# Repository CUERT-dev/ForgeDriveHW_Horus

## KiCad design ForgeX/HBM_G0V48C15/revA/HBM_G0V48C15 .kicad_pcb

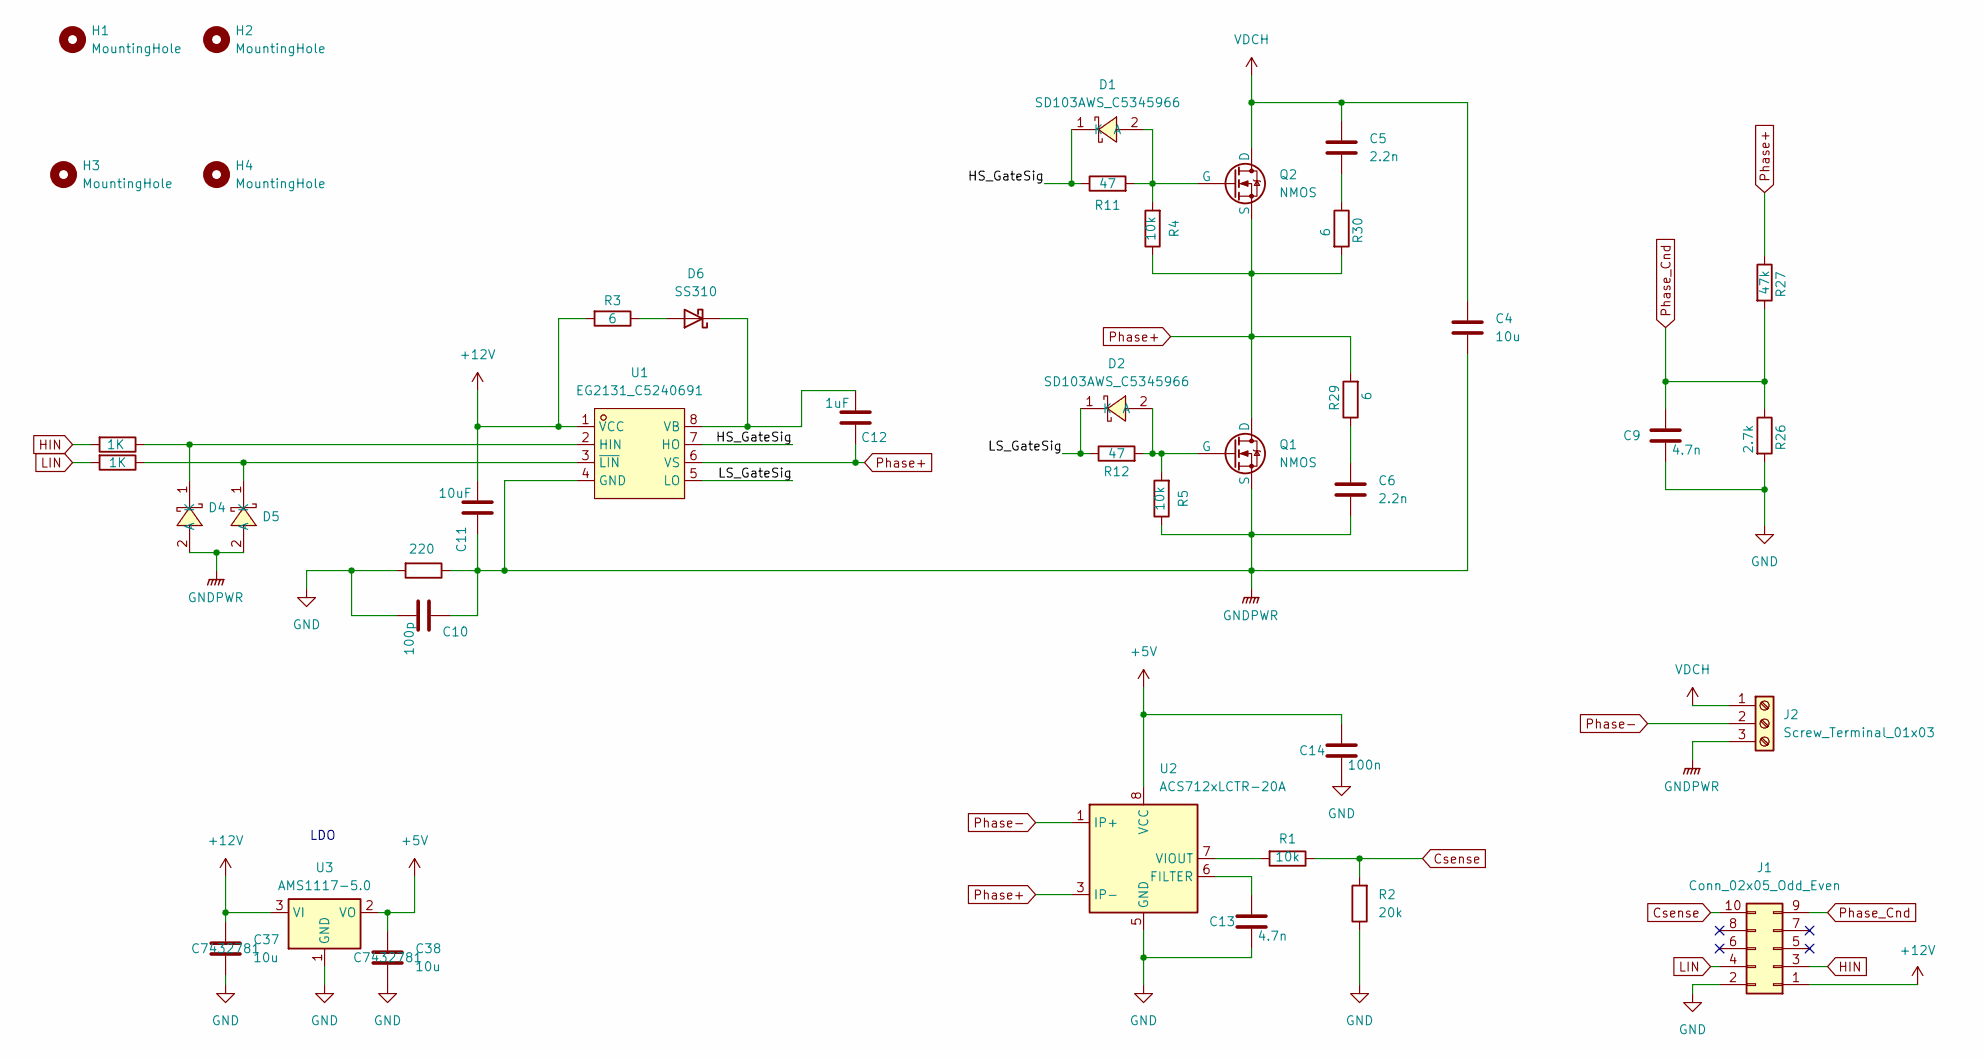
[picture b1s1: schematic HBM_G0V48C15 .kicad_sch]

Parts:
C4: 10u; C_1210_3225Metric_Pad1.33x2.70mm_HandSolder
C5, C6: 2.2n; C_1206_3216Metric_Pad1.33x1.80mm_HandSolder
C9, C13: 4.7n; C_0603_1608Metric_Pad1.08x0.95mm_HandSolder
C10: 100p; C_1206_3216Metric_Pad1.33x1.80mm_HandSolder
C11: 10uF; C_1206_3216Metric_Pad1.33x1.80mm_HandSolder
C12: 1uF; C_1206_3216Metric_Pad1.33x1.80mm_HandSolder
C14: 100n; C_0603_1608Metric_Pad1.08x0.95mm_HandSolder
C37, C38: 10u; C_1206_3216Metric_Pad1.33x1.80mm_HandSolder; LCSC Part C7432781
D1, D2, D4, D5: SD103AWS_C5345966; SOD-323_L1.7-W1.3-LS2.5-RD; MPN SD103AWS; LCSC Part C5345966
D6: SS310; D_SMA
H1, H2: MountingHole; MountingHole_3.2mm_M3_DIN965
H3, H4: MountingHole; MountingHole_2.2mm_M2_DIN965
J1: Conn_02x05_Odd_Even; PinHeader_2x05_P2.54mm_Vertical
J2: Screw_Terminal_01x03; SPACER_M3_PCONN_2x03
Q1, Q2: NMOS; DFN5x6
R1, R4, R5: 10k; R_0603_1608Metric_Pad0.98x0.95mm_HandSolder
R2: 20k; R_0603_1608Metric_Pad0.98x0.95mm_HandSolder
R3: 6; R_0603_1608Metric_Pad0.98x0.95mm_HandSolder
R8: 220; R_1206_3216Metric_Pad1.30x1.75mm_HandSolder
R9, R10: 1K; R_0603_1608Metric_Pad0.98x0.95mm_HandSolder
R11, R12: 47; R_0603_1608Metric_Pad0.98x0.95mm_HandSolder
R26: 2.7k; R_0603_1608Metric_Pad0.98x0.95mm_HandSolder
R27: 47k; R_1206_3216Metric_Pad1.30x1.75mm_HandSolder
R29, R30: 6; R_1206_3216Metric_Pad1.30x1.75mm_HandSolder
U1: EG2131_C5240691; SOP-8_L4.9-W3.9-P1.27-LS6.0-BL; MPN EG2131; LCSC Part C5240691
U2: ACS712xLCTR-20A; SOIC-8_3.9x4.9mm_P1.27mm
U3: AMS1117-5.0; SOT-89-3

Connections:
+5V: C14.1, C38.1, U2.8 (VCC), U3.2 (VO)
+12V: C11.2, C37.1, J1.1, R3.2, U1.1 (VCC), U3.3 (VI)
/HS_GateSig: D1.1 (K), R11.1, U1.7 (HO)
/LS_GateSig: D2.1 (K), R12.1, U1.5 (LO)
Csense: J1.10, R1.1, R2.2
GND: C9.2, C10.2, C13.2, C14.2, C37.2, C38.2, J1.2, R2.1, R8.2, R26.2, U2.5 (GND), U3.1 (GND)
GNDPWR: C4.2, C6.1, C10.1, C11.1, D4.2 (A), D5.2 (A), J2.3, Q1.3 (S), R5.1, R8.1, U1.4 (GND)
HIN: J1.3, R9.2
LIN: J1.4, R10.2
unnamed: C5.2, R30.1
unnamed: C6.2, R29.1
unnamed: D1.2 (A), Q2.2 (G), R4.2, R11.2
unnamed: D2.2 (A), Q1.2 (G), R5.2, R12.2
unnamed: D4.1 (K), R9.1, U1.2 (HIN)
unnamed: D5.1 (K), R10.1, U1.3 (~LIN)
unnamed: D6.2 (A), R3.1
unnamed: C12.2, D6.1 (K), U1.8 (VB)
unnamed: C13.1, U2.6 (FILTER)
unnamed: R1.2, U2.7 (VIOUT)
Phase+: C12.1, Q1.1 (D), Q2.3 (S), R4.1, R27.1, R29.2, R30.2, U1.6 (VS), U2.3 (IP-), U2.4 (IP-)
Phase-: J2.2, U2.1 (IP+), U2.2 (IP+)
Phase_Cnd: C9.1, J1.9, R26.1, R27.2
VDCH: C4.1, C5.1, J2.1, Q2.1 (D)

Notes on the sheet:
LDO

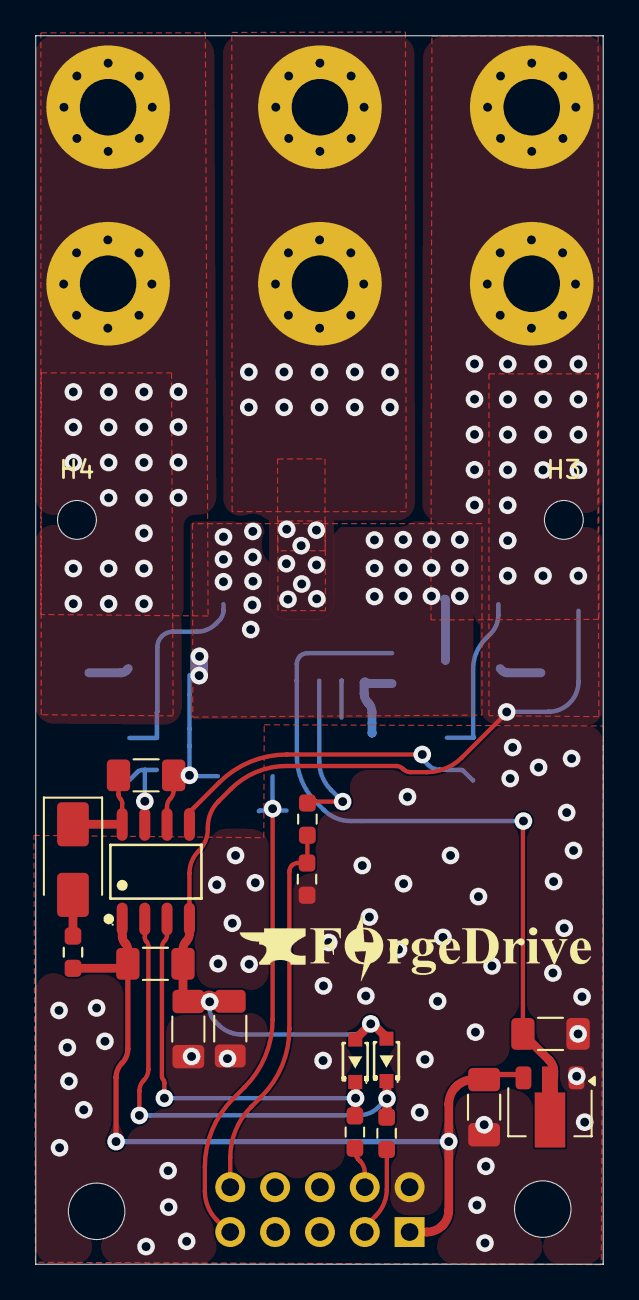
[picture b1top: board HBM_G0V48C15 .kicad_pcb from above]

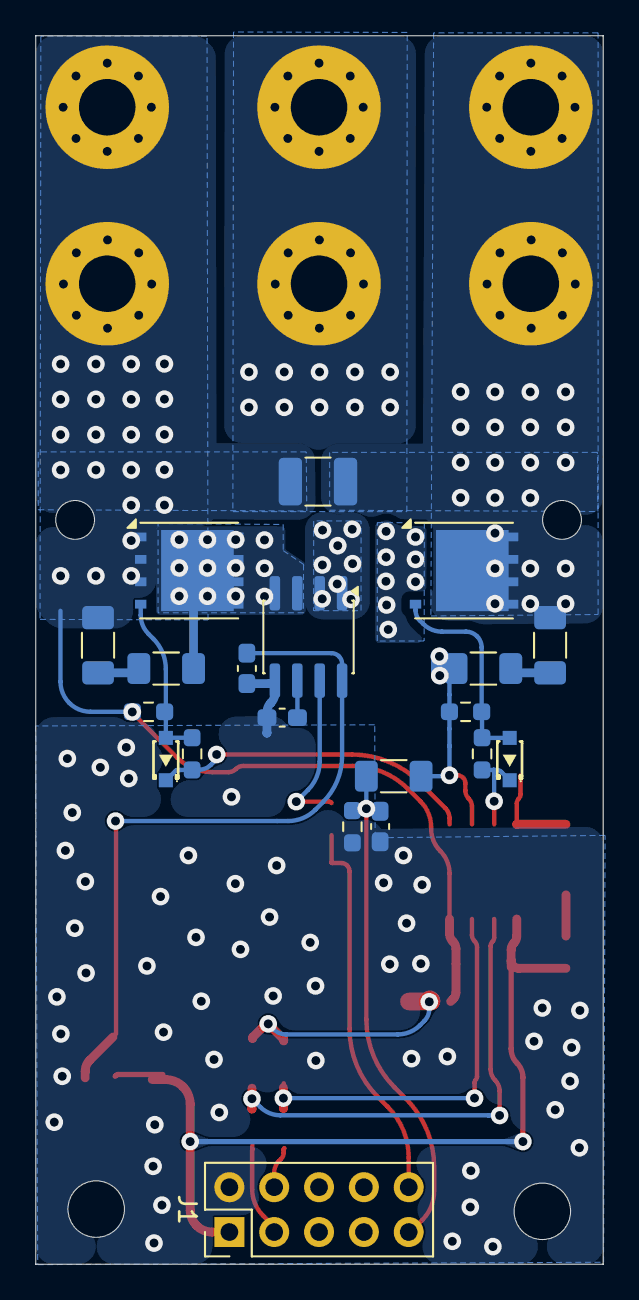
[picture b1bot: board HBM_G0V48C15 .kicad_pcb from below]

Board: 2 copper layers, 32.2 x 69.6 mm, 41 parts (20 on the bottom side), 23 nets.

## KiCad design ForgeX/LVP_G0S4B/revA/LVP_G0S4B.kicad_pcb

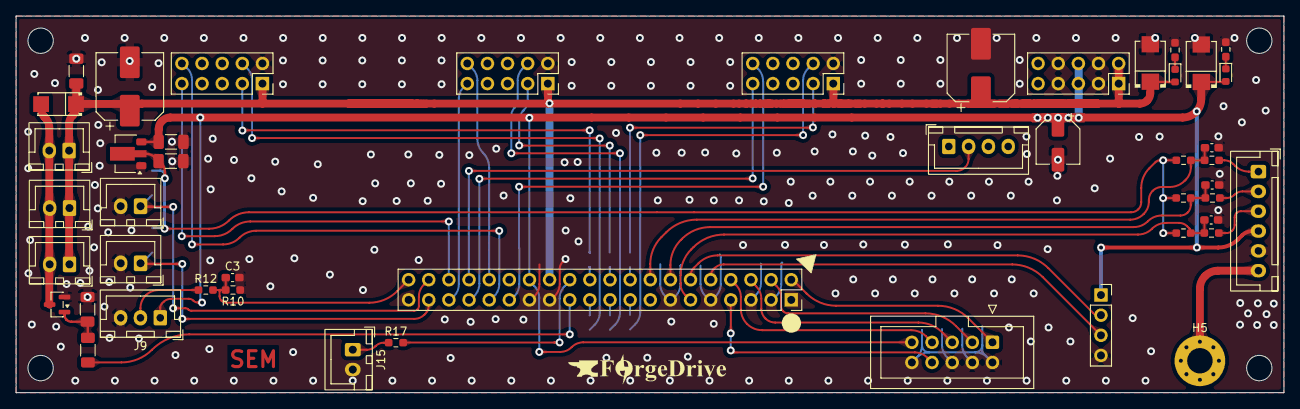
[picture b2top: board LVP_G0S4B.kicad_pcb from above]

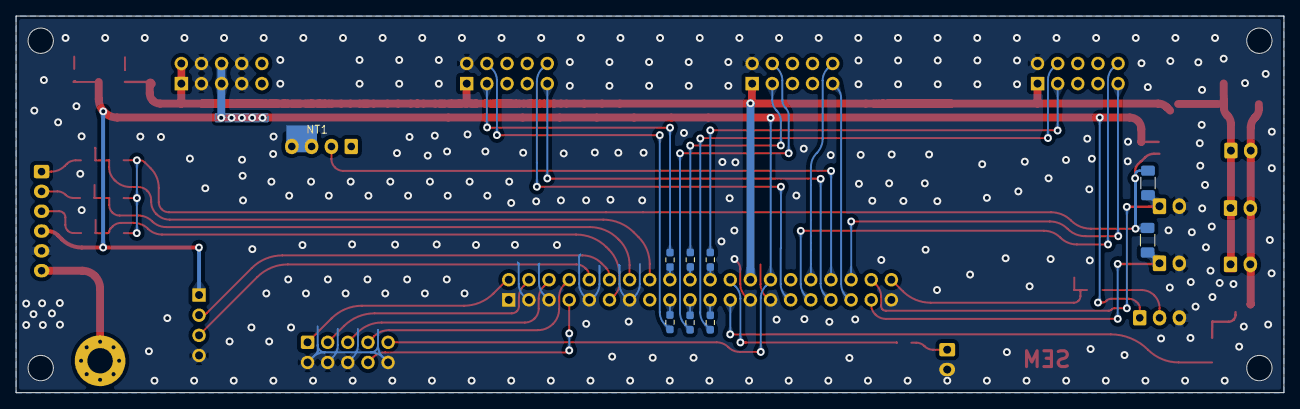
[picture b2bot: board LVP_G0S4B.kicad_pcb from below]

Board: 2 copper layers, 159.9 x 47.5 mm, 60 parts (9 on the bottom side), 49 nets.

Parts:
C1, C2, C6: 10u; C_1206_3216Metric_Pad1.33x1.80mm_HandSolder
C3: 100n; C_0603_1608Metric_Pad1.08x0.95mm_HandSolder
C8: 47uF; CP_Elec_5x5.4
C9, C10: 100uF; CP_Elec_8x6.5
C11, C12, C13: 100p; C_0603_1608Metric_Pad1.08x0.95mm_HandSolder
D1, D3: LED; LED_0603_1608Metric
D2: SS34_C8678; SMA_L4.3-W2.6-LS5.2-RD
D4: SMBJ5.0A_C83333; SMB_L4.6-W3.6-LS5.3-RD
D5: SMBJ12A_C151251; SMB_L4.6-W3.6-LS5.3-RD
H1, H2, H3, H4: MountingHole; MountingHole_3.2mm_M3_DIN965
H5: MountingHole_Pad; MountingHole_3.2mm_M3_Pad_Via
J1, J2, J3, J4: Conn_02x05_Odd_Even; PinSocket_2x05_P2.54mm_Vertical
J5: Conn_01x06_Pin; JST_XH_B6B-XH-A_1x06_P2.50mm_Vertical
J6: Conn_02x20_Odd_Even; PinSocket_2x20_P2.54mm_Vertical
J7, J8, J11, J12, J13, J15: Conn_01x02_Pin; JST_XH_B2B-XH-A_1x02_P2.50mm_Vertical
J9: Conn_01x03_Pin; JST_XH_B3B-XH-A_1x03_P2.50mm_Vertical
J14: Conn_02x05_Odd_Even; IDC-Header_2x05_P2.54mm_Vertical
J16: Conn_01x04; PinSocket_1x04_P2.54mm_Vertical
J17: Conn_01x04; JST_XH_B4B-XH-A_1x04_P2.50mm_Vertical
NT1: NetTie_2; ground_tie
Q2: AO3400A; SOT-23
R1, R2, R3, R4, R5, R6, R14, R15, R18: 220; R_0603_1608Metric_Pad0.98x0.95mm_HandSolder
R7, R16, R17: 1k; R_0603_1608Metric_Pad0.98x0.95mm_HandSolder
R8, R9, R11: 20k; R_1206_3216Metric_Pad1.30x1.75mm_HandSolder
R10: 20k; R_0603_1608Metric_Pad0.98x0.95mm_HandSolder
R12: 10k; R_0603_1608Metric_Pad0.98x0.95mm_HandSolder
R13: 2k; R_1206_3216Metric_Pad1.30x1.75mm_HandSolder
R19, R20, R21: 2.2k; R_0603_1608Metric_Pad0.98x0.95mm_HandSolder
U4: AMS1117-3.3; SOT-89-3

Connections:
+3.3V: C2.1, R8.2, R9.2, R19.2, R20.2, R21.2, U4.2 (VO)
+5V: C1.1, C8.1, D3.2 (A), D4.1, J4.5, J4.6, J5.4, J6.28, J9.1, J14.9, J16.1, U4.3 (VI)
+12V: C6.1, C9.1, C10.1, D1.2 (A), D2.1 (K), D5.1 (K), J1.1, J2.1, J3.1, J4.1, J4.2, J6.26, J11.1, J12.1, J13.1
/Csense_{A}: J3.10, J6.29
/Csense_{B}: J2.10, J6.32
/Csense_{C}: J1.10, J6.31
/ENC_R1: C11.1, J6.16, R14.1, R19.1
/ENC_R1_IN: J5.1, R14.2
/ENC_R2: C12.1, J6.14, R15.1, R20.1
/ENC_R2_IN: J5.2, R15.2
/ENC_R3: C13.1, J6.11, R18.1, R21.1
/ENC_R3_IN: J5.3, R18.2
/EXP_CS0: J6.8, J14.7
/EXP_CS1: J6.7, J14.8
/EXP_MISO: J6.6, J14.5
/EXP_MOSI: J6.4, J14.3
/EXP_RX: J6.12, J16.2
/EXP_SCLK: J6.2, J14.1
/EXP_TX: J6.10, J16.3
/FAN0: J6.23, R13.2
/HIN_{A}: J3.3, R1.2
/HIN_{B}: J2.3, R3.2
/HIN_{C}: J1.3, R4.2
/HVDC_Cnd: J6.34, J17.2
/LIN_{A}: J3.4, R2.1
/LIN_{B}: J2.4, R5.1
/LIN_{C}: J1.4, R6.1
/Phase_Cnd_{A}: J3.9, J6.33
/Phase_Cnd_{B}: J2.9, J6.35
/Phase_Cnd_{C}: J1.9, J6.36
/TEMP1: J6.38, J7.1, R8.1
/TEMP2: J6.37, J8.1, R9.1
/THROTTLE: C3.1, J6.40, R10.2, R12.2
/~BKIN: J6.24, R17.2
Earth: H5.1 (1_1), J5.6
GND: C1.2, C2.2, C3.2, C6.2, C8.2, C9.2, C10.2, C11.2, C12.2, C13.2, D4.2, D5.2 (A), J1.2, J2.2, J3.2, J4.3, J4.4, J4.7, J4.8, J5.5, J6.1, J6.3, J6.5, J6.9, J6.13, J6.25, J6.27, J6.39, J7.2, J8.2, J9.3, J14.2, J14.4, J14.6, J14.10, J15.2, J16.4, NT1.2, Q2.2 (S), R7.2, R10.1, R11.1, R16.2, U4.1 (GND)
GNDPWR: J17.3, J17.4, NT1.1
unnamed: D1.1 (K), R7.1
unnamed: D2.2 (A), J11.2, J12.2, J13.2, Q2.3 (D)
unnamed: D3.1 (K), R16.1
unnamed: J6.17, R2.2
unnamed: J6.18, R1.1
unnamed: J6.19, R5.2
unnamed: J6.20, R3.1
unnamed: J6.21, R6.2
unnamed: J6.22, R4.1
unnamed: J9.2, R12.1
unnamed: J15.1, R17.1
unnamed: Q2.1 (G), R11.2, R13.1

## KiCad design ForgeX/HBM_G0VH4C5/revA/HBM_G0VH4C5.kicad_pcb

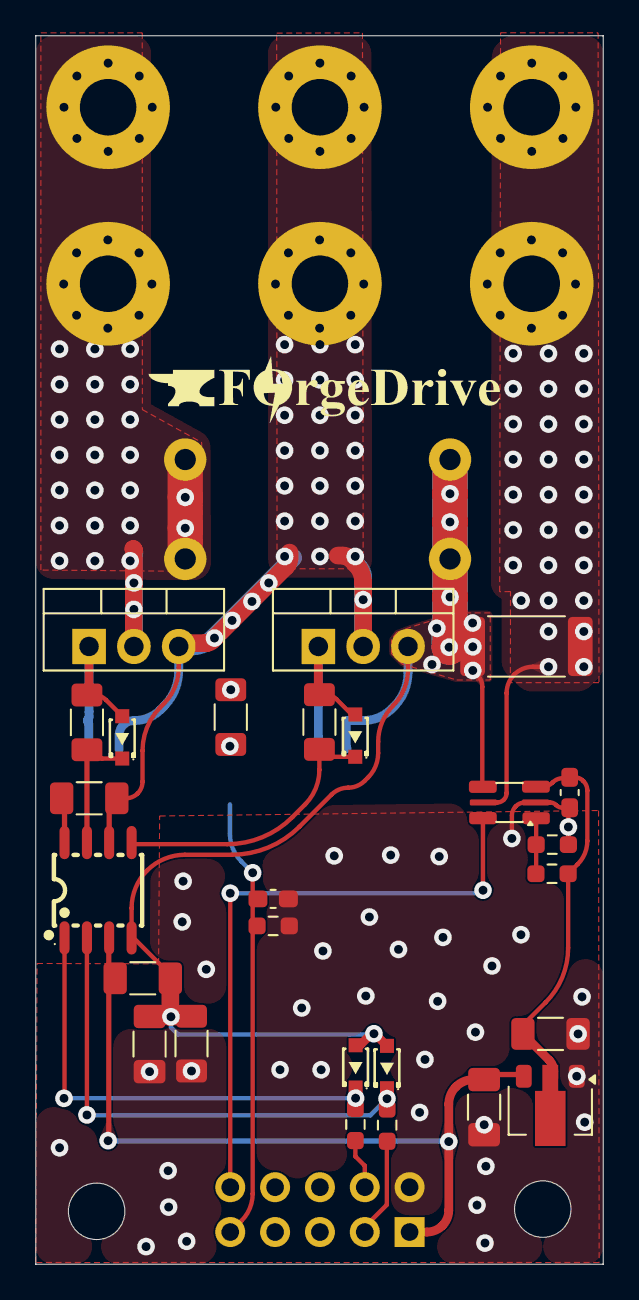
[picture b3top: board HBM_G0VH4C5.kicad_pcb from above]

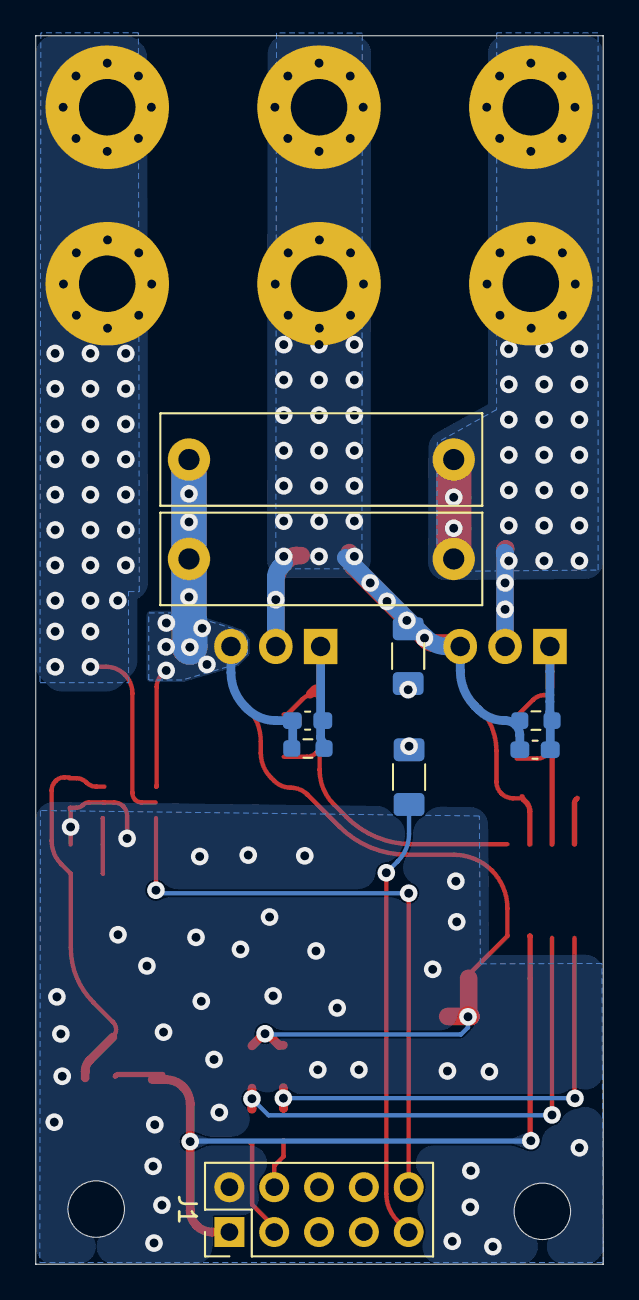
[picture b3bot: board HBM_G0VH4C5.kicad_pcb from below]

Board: 2 copper layers, 32.2 x 69.6 mm, 38 parts (9 on the bottom side), 21 nets.

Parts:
C2, C3: 1n; C_0603_1608Metric_Pad1.08x0.95mm_HandSolder
C4: 0.1u; C_0603_1608Metric_Pad1.08x0.95mm_HandSolder
C7: 10uF; C_1206_3216Metric_Pad1.33x1.80mm_HandSolder
C8: 1u; C_1206_3216Metric_Pad1.33x1.80mm_HandSolder
C9: 47n; C_0603_1608Metric_Pad1.08x0.95mm_HandSolder
C10: 100p; C_1206_3216Metric_Pad1.33x1.80mm_HandSolder
C20, C21: 1u; C_Rect_L18.0mm_W5.0mm_P15.00mm_FKS3_FKP3
C37, C38: 10u; C_1206_3216Metric_Pad1.33x1.80mm_HandSolder
D1, D2, D3, D4: SD103AWS_C5345966; SOD-323_L1.7-W1.3-LS2.5-RD
H1, H2: MountingHole; MountingHole_3.2mm_M3_DIN965
J1: Conn_02x05_Odd_Even; PinHeader_2x05_P2.54mm_Vertical
J2: Screw_Terminal_01x03; SPACER_M3_PCONN_2x03
Q1, Q2: STF24N60M2; TO-220-3_Vertical
R1: 5m; R_2512_6332Metric_Pad1.40x3.35mm_HandSolder
R2, R3, R4, R5: 10k; R_0603_1608Metric_Pad0.98x0.95mm_HandSolder
R6, R7: 1k; R_0603_1608Metric_Pad0.98x0.95mm_HandSolder
R8: 220; R_1206_3216Metric_Pad1.30x1.75mm_HandSolder
R11, R12: 10; R_1206_3216Metric_Pad1.30x1.75mm_HandSolder
R26: 3.3k; R_0603_1608Metric_Pad0.98x0.95mm_HandSolder
R27, R28, R29: 150k; R_1206_3216Metric_Pad1.30x1.75mm_HandSolder
U1: INA199xxDCK; SOT-363_SC-70-6
U3: L6388ED; SO-8_L4.9-W3.9-P1.27-LS5.9-BL
U7: AMS1117-3.3; SOT-89-3

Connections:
+3.3V: C4.1, C38.1, R2.2, U1.3 (V+), U7.2 (VO)
+12V: C7.1, C37.1, J1.1, U3.3 (VCC), U7.3 (VI)
/HS_GateSig: D1.1 (K), R11.1, U3.7 (HVG)
/LS_GateSig: D2.1 (K), R12.1, U3.5 (LVG)
/Shunt+: C2.2, C7.2, C10.1, C20.2, C21.2, D3.2 (A), D4.2 (A), Q1.3 (S), R1.1, R5.1, R8.1, U1.4 (+), U3.4 (GND)
Csense: J1.10, U1.6
GND: C4.2, C9.2, C10.2, C37.2, C38.2, J1.2, R3.1, R8.2, R26.2, U1.2 (GND), U7.1 (GND)
GNDPWR: J2.3, R1.2, U1.5 (-)
HIN: J1.3, R7.1
LIN: J1.4, R6.1
unnamed: C3.1, D1.2 (A), Q2.1 (G), R4.2, R11.2
unnamed: C2.1, D2.2 (A), Q1.1 (G), R5.2, R12.2
unnamed: D3.1 (K), R7.2, U3.2 (HIN)
unnamed: D4.1 (K), R6.2, U3.1 (LIN)
unnamed: R27.2, R28.1
unnamed: R28.2, R29.1
unnamed: R2.1, R3.2, U1.1 (REF)
unnamed: C8.1, U3.8 (VBOOT)
Phase: C3.2, C8.2, J2.2, Q1.2 (D), Q2.3 (S), R4.1, R29.2, U3.6 (OUT)
Phase_Cnd: C9.1, J1.9, R26.1, R27.1
VDCH: C20.1, C21.1, J2.1, Q2.2 (D)

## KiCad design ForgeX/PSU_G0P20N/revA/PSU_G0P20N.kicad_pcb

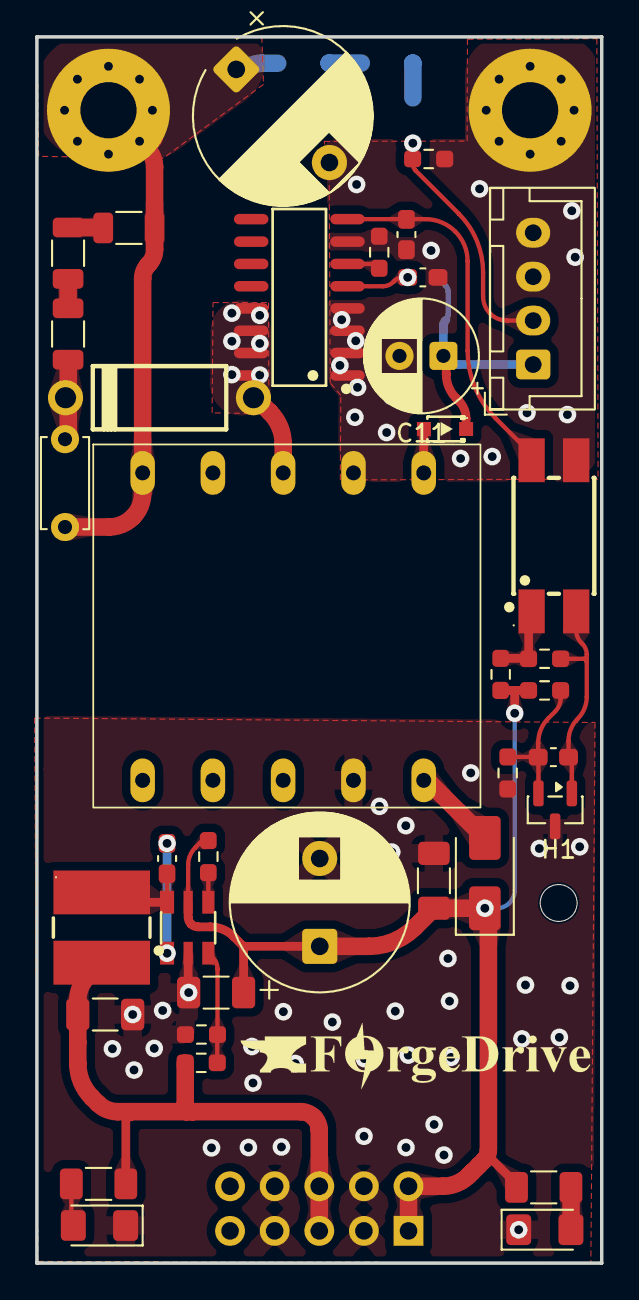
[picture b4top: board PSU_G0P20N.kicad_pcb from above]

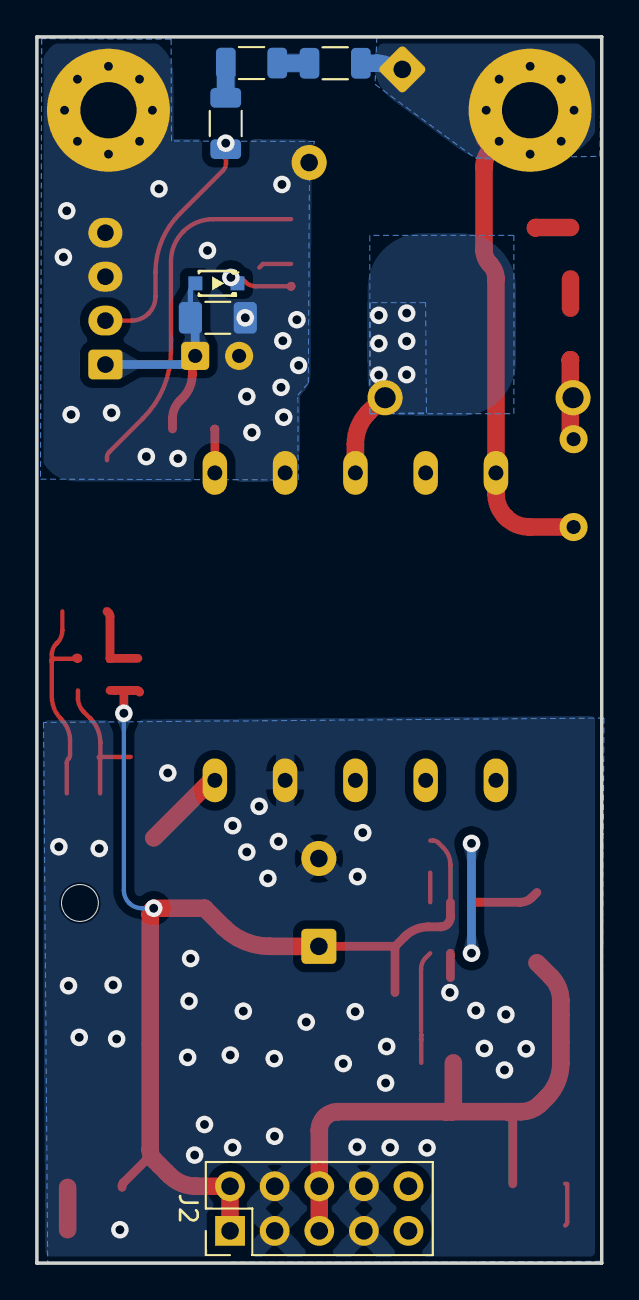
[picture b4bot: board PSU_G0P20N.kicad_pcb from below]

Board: 2 copper layers, 32.1 x 69.8 mm, 45 parts (6 on the bottom side), 27 nets.

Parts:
C1, C3, C10: 10u; C_1206_3216Metric_Pad1.33x1.80mm_HandSolder
C2: 220nF; C_0603_1608Metric_Pad1.08x0.95mm_HandSolder
C4: 2200u; CP_Radial_D10.0mm_P5.00mm
C5: 2.2n; C_Disc_D5.0mm_W2.5mm_P5.00mm
C6: 100p; C_0603_1608Metric_Pad1.08x0.95mm_HandSolder
C7: 47u; CP_Radial_D10.0mm_P7.50mm
C8: 22n; C_0603_1608Metric_Pad1.08x0.95mm_HandSolder
C9: 22u; C_1206_3216Metric_Pad1.33x1.80mm_HandSolder
C11: 220u; CP_Radial_D6.3mm_P2.50mm
C12: 100n; C_0603_1608Metric_Pad1.08x0.95mm_HandSolder
D1: SS36; D_SMA
D3: BYV26EGP-E3/73; DO-15_BD3.1-L6.7-P10.70-D0.9-FD
D4, D5: LED; LED_1206_3216Metric_Pad1.42x1.75mm_HandSolder
D7, D8: SD103AWS_C5345966; SOD-323_L1.7-W1.3-LS2.5-RD
H1: MountingHole; MountingHole_2.1mm
J1: Screw_Terminal_01x02; SPACER_M3_PCONN_PSU
J2: Conn_02x05_Odd_Even; PinHeader_2x05_P2.54mm_Vertical
J4: Conn_01x04; JST_XH_B4B-XH-A_1x04_P2.50mm_Vertical
L2: CD54-6R8M; IND-SMD_L5.8-W5.2_CD54
R1: 1k; R_1206_3216Metric_Pad1.30x1.75mm_HandSolder
R2: 5k; R_1206_3216Metric_Pad1.30x1.75mm_HandSolder
R7: 1.2k; R_0603_1608Metric_Pad0.98x0.95mm_HandSolder
R8: 38k; R_0603_1608Metric_Pad0.98x0.95mm_HandSolder
R9, R17: 10k; R_0603_1608Metric_Pad0.98x0.95mm_HandSolder
R10, R11, R19: 27k; R_1206_3216Metric
R12: 1k; R_0603_1608Metric_Pad0.98x0.95mm_HandSolder
R13: 100k; R_0603_1608Metric_Pad0.98x0.95mm_HandSolder
R14: 15k; R_0603_1608Metric_Pad0.98x0.95mm_HandSolder
R15: 110k; R_0603_1608Metric_Pad0.98x0.95mm_HandSolder
R20, R21, R22: 150k; R_1206_3216Metric
R23: 3.3k; R_0603_1608Metric_Pad0.98x0.95mm_HandSolder
U1: VIPER26LDTR; SOIC-16_L9.9-W3.9-P1.27-LS6.0-BL
U2: TL431DBZ; SOT-23
U3: E22 Trans
U4: PC817SC_C20612450; OPTO-SMD-4_L4.6-W6.5-P2.54-LS10.3-TL
U5: MT2492; SOT-23-6_L2.9-W1.6-P0.95-LS2.8-BL_3

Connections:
+5V: C9.1, J2.5, J2.6, L2.2, R1.1, R15.1
+12V: C1.1, C4.1, C10.1, D1.1 (K), J2.1, J2.2, R2.1, R7.1, R8.1, R17.1, U5.5 (IN)
/Aux: C3.1, C11.1, D7.1 (K), D8.2 (A), J4.1
/Aux_CNTRL: C12.1, D8.1 (K), U1.5 (VDD)
/COMP: C6.2, U1.8 (COMP), U4.4 (COL)
/VDCH: C5.1, C7.1, J1.1, R11.2, R20.2, U3.1
/VDCH_CND: J4.2, R22.1, R23.2
GND: C1.2, C4.2, C9.2, C10.2, D4.1 (K), D5.1 (K), J2.3, J2.4, J2.7, J2.8, R9.2, R14.2, U2.3 (A), U3.6 (S1), U5.2 (GND)
GNDPWR: C3.2, C6.1, C7.2, C11.2, C12.2, J1.2, J4.3, J4.4, R13.1, R23.1, U1.1 (GND), U1.2 (GND), U1.3 (N.C.), U1.4 (N.A.), U1.7 (FB), U3.4 (A1), U4.3 (EM)
unnamed: D1.2 (A), U3.5 (S1)
unnamed: D3.1 (A), U1.13 (DRAIN), U1.14 (DRAIN), U1.15 (DRAIN), U1.16 (DRAIN), U3.2 (P1)
unnamed: C5.2, D3.2 (C), R10.1
unnamed: D4.2 (A), R1.2
unnamed: D5.2 (A), R2.2
unnamed: D7.2 (A), U3.3 (A1)
unnamed: R10.2, R19.1
unnamed: R11.1, R19.2
unnamed: R20.1, R21.2
unnamed: R21.1, R22.2
unnamed: R13.2, U1.6 (LIM)
unnamed: C2.2, R12.2, U2.1 (K), U4.2 (CAT)
unnamed: C2.1, R8.2, R9.1, U2.2 (REF)
unnamed: R7.2, R12.1, U4.1 (AN)
unnamed: C8.2, U5.1 (BS)
unnamed: R17.2, U5.4 (EN)
unnamed: R14.1, R15.2, U5.3 (FB)
unnamed: C8.1, L2.1, U5.6 (SW)

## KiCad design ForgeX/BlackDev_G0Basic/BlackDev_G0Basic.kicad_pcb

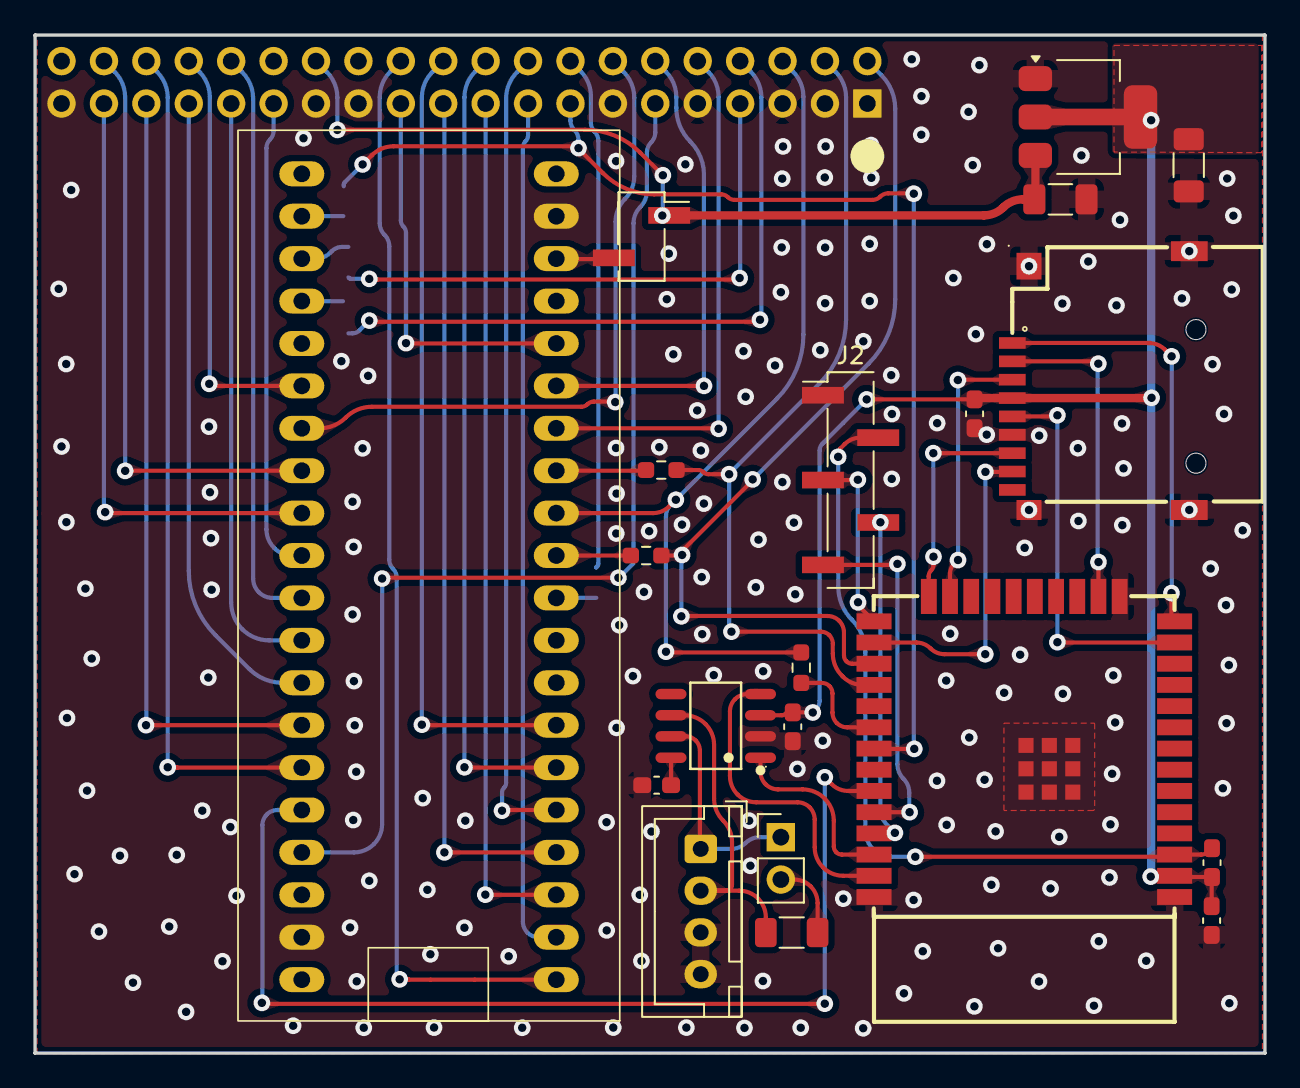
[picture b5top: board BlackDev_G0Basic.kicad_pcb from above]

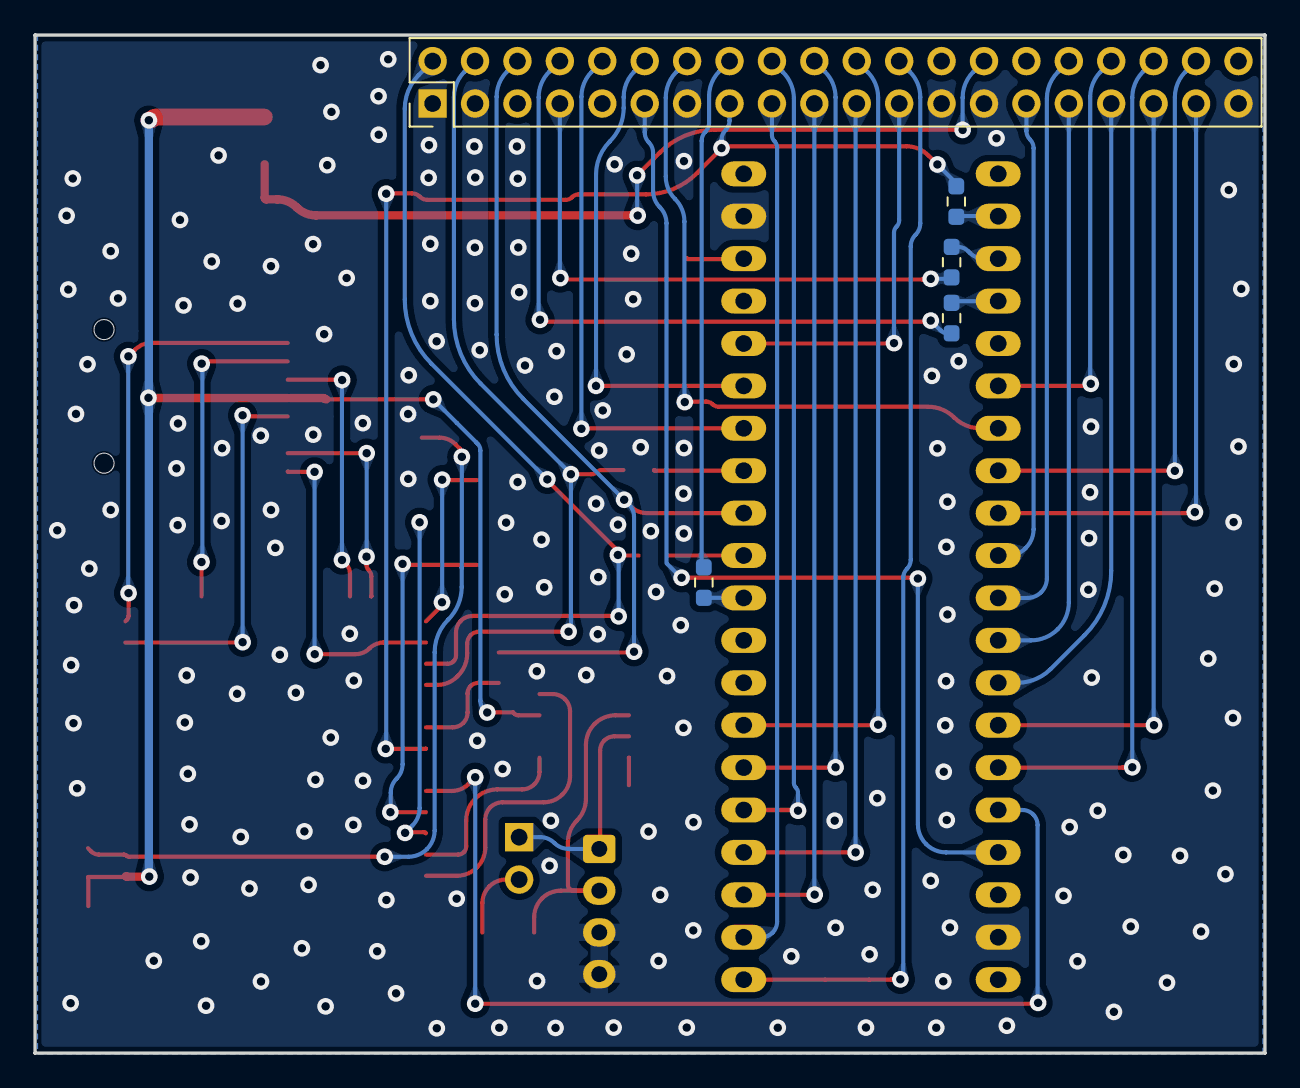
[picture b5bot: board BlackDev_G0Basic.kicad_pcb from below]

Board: 2 copper layers, 73.7 x 61.0 mm, 25 parts (5 on the bottom side), 56 nets.

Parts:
C1, C2: 10u; C_1206_3216Metric_Pad1.33x1.80mm_HandSolder
C3: 100n; C_0603_1608Metric_Pad1.08x0.95mm_HandSolder
C4, C5: 1u; C_0603_1608Metric_Pad1.08x0.95mm_HandSolder
J1: Conn_01x02_Pin; PinHeader_1x02_P2.54mm_Vertical_SMD_Pin1Right
J2: PROG; PinHeader_1x05_P2.54mm_Vertical_SMD_Pin1Left
J3: Conn_01x02_Pin; PinHeader_1x02_P2.54mm_Vertical
J4: Conn_01x04_Pin; JST_XH_B4B-XH-A_1x04_P2.50mm_Vertical
J6: Conn_02x20_Odd_Even; PinHeader_2x20_P2.54mm_Vertical
R1, R2, R3: 4.7k; R_0603_1608Metric_Pad0.98x0.95mm_HandSolder
R4, R6, R7, R12: 22; R_0603_1608Metric_Pad0.98x0.95mm_HandSolder
R9, R11: 10k; C_0603_1608Metric_Pad1.08x0.95mm_HandSolder
R10: 120; R_1206_3216Metric_Pad1.30x1.75mm_HandSolder
U1: Stm32BlackPill
U2: ESP32-WROOM-32E; WIFI-SMD_ESP32-WROOM-32E
U3: AMS1117-3.3; SOT-223-3_TabPin2
U4: SIT65HVD230DR; SOP-8_L4.9-W3.9-P1.27-LS6.0-BL
U5: HX TF PUSH; TF-SMD_TF-PUSH

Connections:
/3.3V: C1.1, C3.1, C4.1, C5.1, R9.2, U2.2 (3V3), U3.2 (VO), U4.3 (VCC), U5.4 (VDD)
/5V: C2.1, J1.1, J6.28, U3.3 (VI)
/Boot0: J2.3, U2.25 (IO0)
/CANH: J3.1, J4.1, U4.7 (CANH)
/CANL: J4.2, R10.1, U4.6 (CANL)
/CAN_RXD: U2.37 (IO23), U4.4 (R)
/CAN_TXD: U2.36 (IO22), U4.1 (D)
/Csense_{A}: J6.29, U1.30 (PA4)
/Csense_{B}: J6.32, U1.31 (PA5)
/Csense_{C}: J6.31, U1.32 (PA6)
/ENC_R1: J6.16, R7.1
/ENC_R2: J6.14, U1.27 (PA1)
/ENC_R3: J6.11, U1.37 (PB10)
/ESP_IRQ: U1.36 (PB2), U2.33 (IO21)
/ESP_RST: J2.2, R9.1, U2.3 (EN)
/EXP_CS0: J6.8, R1.2
/EXP_CS1: J6.7, R2.2
/EXP_CS2: J6.15, R3.2, U2.31 (IO19)
/EXP_MISO: J6.6, R12.2, U1.12 (PB4)
/EXP_MOSI: J6.4, R6.1, U2.28 (IO17)
/EXP_RX: J6.12, U1.15 (PB7)
/EXP_SCLK: J6.2, R4.1, U2.27 (IO16)
/EXP_TX: J6.10, U1.14 (PB6)
/FAN0: J6.23, U1.16 (PB8)
/GND: C1.2, C2.2, C3.2, C4.2, C5.2, J2.1, J4.3, J4.4, J6.1, J6.3, J6.5, J6.9, J6.13, J6.25, J6.27, J6.39, R11.1, U1.19 (Gnd), U1.39 (Gnd), U2.1 (GND), U2.15 (GND), U2.38 (GND), U2.39 (GND), U3.1 (GND), U4.2 (GND), U5.6 (VSS), U5.10 (SHELL), U5.11 (SHELL), U5.12 (SHELL), U5.13 (SHELL)
/HIN_{A}: J6.18, U1.5 (PA8)
/HIN_{B}: J6.20, U1.6 (PA9)
/HIN_{C}: J6.22, U1.7 (PA10)
/HVDC_Cnd: J6.34, U1.26 (PA0)
/LIN_{A}: J6.17, U1.2 (PB13)
/LIN_{B}: J6.19, U1.3 (PB14)
/LIN_{C}: J6.21, U1.4 (PB15)
/Phase_Cnd_{A}: J6.33, U1.33 (PA7)
/Phase_Cnd_{B}: J6.35, U1.34 (PB0)
/Phase_Cnd_{C}: J6.36, U1.35 (PB1)
/SD_CLK: U2.13 (IO14), U5.5 (CLK)
/SD_CMD: U2.23 (IO15), U5.3 (CMD)
/SD_DAT0: U2.24 (IO2), U5.7 (DAT0)
/SD_DAT1: U2.26 (IO4), U5.8 (DAT1)
/SD_DAT2: U2.14 (IO12), U5.1 (DAT2)
/SD_DAT3: U2.16 (IO13), U5.2 (CD/DAT3)
/TEMP1: J6.38, U1.28 (PA2)
/TEMP2: J6.37, U1.29 (PA3)
/~BKIN: J6.24, U1.1 (PB12)
unnamed: J1.2, U1.18 (5V)
unnamed: J2.4, U2.35 (TXD0)
unnamed: J2.5, U2.34 (RXD0)
unnamed: J3.2, R10.2
unnamed: R7.2, U1.10 (PA15)
unnamed: R4.2, U1.11 (PB3)
unnamed: R6.2, U1.13 (PB5)
unnamed: R3.1, U1.22 (PC13)
unnamed: R2.1, U1.23 (PC14)
unnamed: R1.1, U1.24 (PC15)
unnamed: R12.1, U2.30 (IO18)
unnamed: R11.2, U4.8 (RS)
